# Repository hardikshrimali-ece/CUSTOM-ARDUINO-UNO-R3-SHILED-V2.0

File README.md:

# CUSTOM-ARDUINO-UNO-R3-SHILED-V2.0
Arduino UNO Universal Shield V2

User Manual & Developer Guide

Chapter 1 – Introduction

- Purpose of the shield
- Features
- Specifications
- Board overview
- Supported Arduino boards

Chapter 2 – Safety

- Reverse polarity protection
- Voltage limits
- Current limits
- Handling precautions

Chapter 3 – Hardware Layout

- Top view
- Bottom view
- Pin labels
- Connector locations
- Component locations

Chapter 4 – Pin Mapping

Feature| Arduino Pin
MAX7219 DIN| D11
MAX7219 CLK| D13
MAX7219 LOAD| D10
MAX7219 DOUT| D1
Buzzer| D9
SW1| D7
SW2| D6
SW3| D5
SW4| D4

Chapter 5 – Headers

- UART
- I2C
- SPI
- Analog
- Digital
- Power

Explain what every header is used for.

Chapter 6 – Example Programs

Example 1: MAX7219 Display Demo.
/*
  Arduino Shield V2.0
  Example 1 - MAX7219 Display Demo

  DIN  -> D11
  CLK  -> D13
  CS   -> D10
*/

#include <LedControl.h>

#define DIN_PIN 11
#define CLK_PIN 13
#define CS_PIN 10

LedControl lc = LedControl(DIN_PIN, CLK_PIN, CS_PIN, 1);

void setup()
{
  lc.shutdown(0, false);     // Wake display
  lc.setIntensity(0, 8);     // Brightness (0-15)
  lc.clearDisplay(0);
}

void loop()
{
  // Count from 0000 to 9999
  for (int i = 0; i <= 9999; i++)
  {
    displayNumber(i);
    delay(5);
  }

  delay(1000);

  // Display HELLO
  lc.clearDisplay(0);

  lc.setChar(0, 4, 'H', false);
  lc.setChar(0, 3, 'E', false);
  lc.setChar(0, 2, 'L', false);
  lc.setChar(0, 1, 'L', false);
  lc.setChar(0, 0, 'O', false);

  delay(3000);

  lc.clearDisplay(0);

  // Countdown
  for (int i = 9; i >= 0; i--)
  {
    lc.clearDisplay(0);
    lc.setDigit(0, 0, i, false);
    delay(500);
  }

  lc.clearDisplay(0);
}

void displayNumber(int number)
{
  lc.setDigit(0, 0, number % 10, false);
  lc.setDigit(0, 1, (number / 10) % 10, false);
  lc.setDigit(0, 2, (number / 100) % 10, false);
  lc.setDigit(0, 3, (number / 1000) % 10, false);
}

Example 2 – Button Test (D7, D6, D5, D4)
This example verifies that all four push buttons on your shield are working.

/*
  Arduino Shield V2.0
  Example 2 - Button Test

  Button 1 -> D7
  Button 2 -> D6
  Button 3 -> D5
  Button 4 -> D4
*/

#define BTN1 7
#define BTN2 6
#define BTN3 5
#define BTN4 4

void setup()
{
  Serial.begin(9600);

  pinMode(BTN1, INPUT_PULLUP);
  pinMode(BTN2, INPUT_PULLUP);
  pinMode(BTN3, INPUT_PULLUP);
  pinMode(BTN4, INPUT_PULLUP);

  Serial.println("=== Arduino Shield Button Test ===");
  Serial.println("Press any button...");
}

void loop()
{
  if (digitalRead(BTN1) == LOW)
  {
    Serial.println("Button 1 Pressed");
    delay(200);
  }

  if (digitalRead(BTN2) == LOW)
  {
    Serial.println("Button 2 Pressed");
    delay(200);
  }

  if (digitalRead(BTN3) == LOW)
  {
    Serial.println("Button 3 Pressed");
    delay(200);
  }

  if (digitalRead(BTN4) == LOW)
  {
    Serial.println("Button 4 Pressed");
    delay(200);
  }
}

Example 2 – reaction time game 
uses: 
 - 4 digit 7 segment display
 - buzzer
 - button 1 (D7)

 #include <LedControl.h>

#define DIN 11
#define CLK 13
#define CS 10

#define BUZZER 9
#define BUTTON 7

LedControl lc = LedControl(DIN, CLK, CS, 1);

unsigned long startTime;
unsigned long reaction;

void setup()
{
  pinMode(BUTTON, INPUT_PULLUP);
  pinMode(BUZZER, OUTPUT);

  lc.shutdown(0, false);
  lc.setIntensity(0, 8);
  lc.clearDisplay(0);

  randomSeed(analogRead(A0));
}

void loop()
{
  // Ready
  showText("GO");

  delay(2000);

  lc.clearDisplay(0);

  // Random wait
  delay(random(2000, 5000));

  // Beep
  tone(BUZZER, 1000, 150);

  // Show 0000
  displayNumber(0);

  startTime = millis();

  while (digitalRead(BUTTON) == HIGH);

  reaction = millis() - startTime;

  displayNumber(reaction);

  delay(5000);
}

void displayNumber(int num)
{
  lc.setDigit(0, 0, num % 10, false);
  lc.setDigit(0, 1, (num / 10) % 10, false);
  lc.setDigit(0, 2, (num / 100) % 10, false);
  lc.setDigit(0, 3, (num / 1000) % 10, false);
}

void showText(String txt)
{
  lc.clearDisplay(0);

  if (txt == "GO")
  {
    lc.setChar(0, 1, 'G', false);
    lc.setChar(0, 0, 'O', false);
  }
}

Example 4 - countdown timer 
uses: 
- display
- button 1
- buzzer

Chapter 7 – Libraries Required

- LedControl
- MD_MAX72XX
- SPI
- Wire

Explain why each library is used.

Chapter 8 – Troubleshooting

Troubleshooting Guide

The display does not turn ON

Possible reasons

- Arduino is not powered.
- Shield is not inserted properly.

What to do

1. Make sure the Arduino is powered.
2. Check that the shield is firmly connected.
3. Upload the example sketch again./*
  Arduino Shield V2.0
  Example 4 - Countdown Timer

  Button 1 -> Start Countdown
*/

#include <LedControl.h>

#define DIN     11
#define CLK     13
#define CS      10

#define BUTTON  7
#define BUZZER  9

LedControl lc = LedControl(DIN, CLK, CS, 1);

void setup()
{
  pinMode(BUTTON, INPUT_PULLUP);
  pinMode(BUZZER, OUTPUT);

  lc.shutdown(0, false);
  lc.setIntensity(0, 8);
  lc.clearDisplay(0);

  displayNumber(10);   // Initial countdown value
}

void loop()
{
  if (digitalRead(BUTTON) == LOW)
  {
    countdown(10);

    delay(1000);
  }
}

void countdown(int seconds)
{
  for (int i = seconds; i >= 0; i--)
  {
    displayNumber(i);
    delay(1000);
  }

  // Alarm
  for (int i = 0; i < 3; i++)
  {
    tone(BUZZER, 1000);
    delay(200);

    noTone(BUZZER);
    delay(200);
  }

  displayNumber(10);
}

void displayNumber(int num)
{
  lc.setDigit(0, 0, num % 10, false);
  lc.setDigit(0, 1, (num / 10) % 10, false);
  lc.setDigit(0, 2, (num / 100) % 10, false);
  lc.setDigit(0, 3, (num / 1000) % 10, false);
}

---

The display shows incorrect numbers

Possible reasons

- Incorrect program uploaded.
- Display initialization failed.

What to do

1. Restart the Arduino.
2. Upload the example program provided.
3. Ensure the display module is inserted correctly.

---

The buzzer does not make any sound

Possible reasons

- Buzzer disabled in the program.
- Buzzer is damaged.

What to do

1. Run the buzzer example program.
2. Restart the Arduino.
3. If there is still no sound, contact support.

---

Push buttons are not responding

Possible reasons

- Program is not running.
- Button is being pressed too quickly.

What to do

1. Restart the Arduino.
2. Press the button firmly once.
3. Test using the button example sketch.

---

I2C module is not working

What to do

1. Check that the sensor is connected to the I2C header.
2. Verify the sensor wiring.
3. Use an I2C Scanner sketch to detect the device.

---

UART module is not working

What to do

1. Ensure the TX and RX connections are correct.
2. Verify the baud rate in your program.
3. Restart both devices.

---

SPI module is not working

What to do

1. Ensure the module is connected to the SPI header.
2. Verify the program supports the connected module.
3. Restart the Arduino.

---

Arduino does not detect the shield

What to do

1. Remove the shield.
2. Reinsert it carefully.
3. Ensure all header pins are aligned correctly.

Board becomes hot

Warning
Disconnect power immediately.

Possible reasons

- Incorrect power supply.
- Short circuit.
- Incorrect wiring.

Do not continue using the board until the issue is identified.

Nothing works

1. Disconnect power.
2. Wait 10 seconds.
3. Reconnect power.
4. Upload the example sketch.
5. Test each feature one by one.

Please check the following:

- ✔ Arduino is powered.
- ✔ Shield is inserted correctly.
- ✔ Correct example sketch is uploaded.
- ✔ All modules are connected properly.
- ✔ USB cable is working.
- ✔ Arduino board is detected by the Arduino IDE.

If the problem still exists, provide:

- Shield version
- Arduino model
- Example program used
- Clear photos of the setup
- Description of the problem

Chapter 9 – PCB Features

- 2-layer PCB
- Reverse polarity protection
- Standard Arduino shield layout
- Stackable headers
- Universal expansion connectors

Chapter 10 – Revision History

V1.0

- Initial board

V2.0

- Added reverse polarity protection
- Added buzzer
- Added push buttons
- Added UART/I2C/SPI headers
- Improved layout

Chapter 11 – Future Expansion

- OLED
- NRF24L01
- GPS
- IMU
- Bluetooth
- Wi-Fi
- Sensors

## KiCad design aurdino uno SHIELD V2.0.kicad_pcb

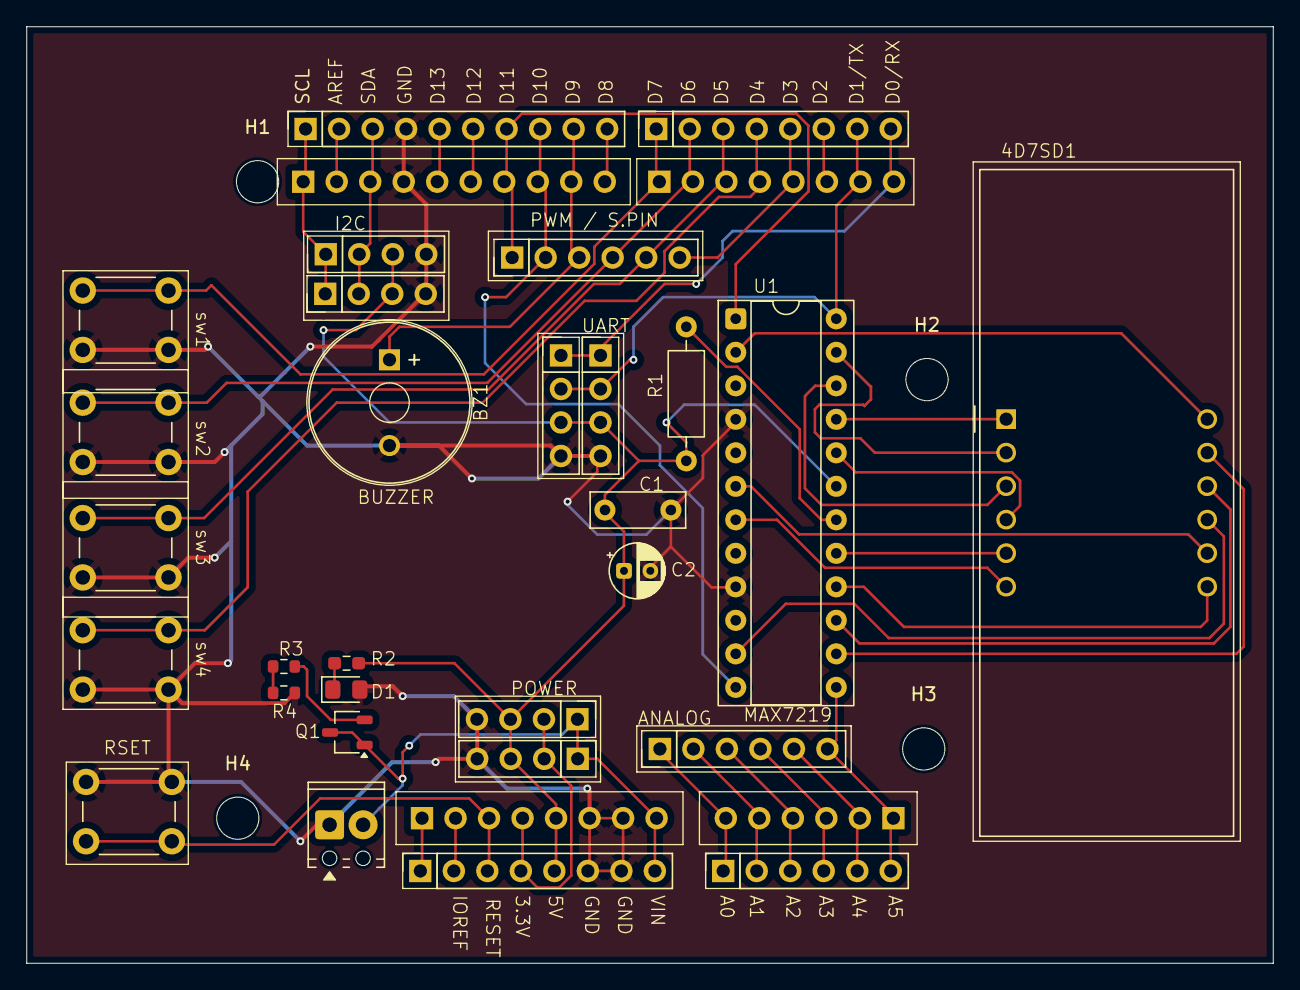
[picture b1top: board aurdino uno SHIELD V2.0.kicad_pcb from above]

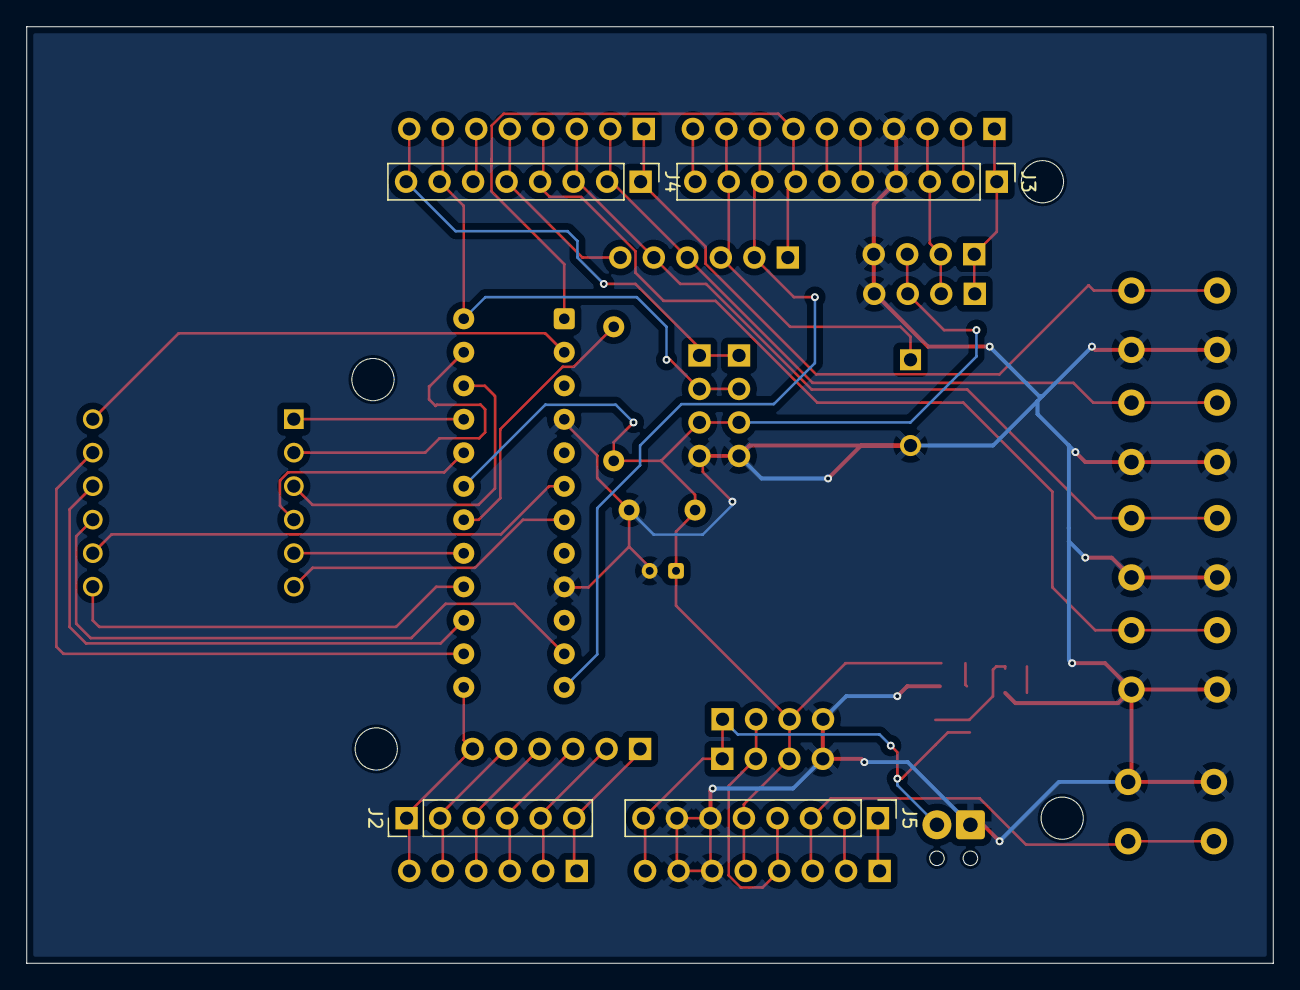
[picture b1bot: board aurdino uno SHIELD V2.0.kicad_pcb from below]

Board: 2 copper layers, 94.5 x 71.0 mm, 37 parts (4 on the bottom side), 43 nets.

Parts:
4D7SD1: CC56-12EWA; CA56-12EWA
BZ1: Buzzer; MagneticBuzzer_ProSignal_ABT-410-RC
C1: 0.1mF; C_Disc_D7.0mm_W2.5mm_P5.00mm
C2: 10mF; CP_Radial_D4.0mm_P2.00mm
D1: LED; LED_0805_2012Metric_Pad1.15x1.40mm_HandSolder
H1, H2, H3, H4: MountingHole; MountingHole_3.2mm_M3
I2C1, I2C2: I2C; PinHeader_1x04_P2.54mm_Vertical
J1: VIN 5V; TerminalBlock_Phoenix_MPT-0,5-2-2.54_1x02_P2.54mm_Horizontal
J2: ANALOG; PinHeader_1x06_P2.54mm_Vertical
J3: digital01; PinHeader_1x10_P2.54mm_Vertical
J4: digital02; PinHeader_1x08_P2.54mm_Vertical
J5: ANALOG01; PinHeader_1x08_P2.54mm_Vertical
J6: analog02; PinHeader_1x06_P2.54mm_Vertical
J7: digital01d; PinSocket_1x10_P2.54mm_Vertical
J8: digital02D; PinSocket_1x08_P2.54mm_Vertical
J9: ANALOG01D; PinSocket_1x08_P2.54mm_Vertical
J10: analog02; PinSocket_1x06_P2.54mm_Vertical
P1, P2, P3, P4: SW_Push; SW_PUSH_6mm_H5mm
PWR1, PWR2: I2C; PinHeader_1x04_P2.54mm_Vertical
Q1: PMOS_Substrate; TSOT-23
R1: 10k; R_Axial_DIN0207_L6.3mm_D2.5mm_P10.16mm_Horizontal
R2: 1.2k; R_0603_1608Metric_Pad0.98x0.95mm_HandSolder
R3: 100k; R_0603_1608Metric
R4: 100; R_0603_1608Metric
RSET1: SW_Push; SW_PUSH_6mm_H5mm
SPIN1: PWM; PinHeader_1x06_P2.54mm_Vertical
U1: MAX7219; DIP-24_W7.62mm_Socket
UART1, UART2: I2C; PinHeader_1x04_P2.54mm_Vertical

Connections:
3.3V: J5.4, J9.4, PWR1.2, PWR2.2
5V: C1.1, C2.1, I2C1.3, I2C2.3, J5.5, J9.5, PWR1.3, PWR2.3, R1.2, R2.2, U1.19 (V+), UART1.3, UART2.3
A0: J2.6, J6.1, J10.1
A1: J2.5, J6.2, J10.2
A2: J2.4, J6.3, J10.3
A3: J2.3, J6.4, J10.4
A4: J2.2, J6.5, J10.5
A5: J2.1, J6.6, J10.6, U1.13 (CLK)
D2: J4.6, J8.6
D3: J4.5, J8.5, SPIN1.6
D4: J4.4, J8.4, P4.1
D5: J4.3, J8.3, P3.1, SPIN1.5
D6: J4.2, J8.2, P2.1, SPIN1.4
D7: J4.1, J8.1, P1.1
D8: J3.10, J7.10
D9: BZ1.1 (+), J3.9, J7.9, SPIN1.3
D10: J3.8, J7.8, SPIN1.2, U1.12 (LOAD)
D11: J3.7, J7.7, SPIN1.1, U1.1 (DIN)
D12: J3.6, J7.6
D13: J3.5, J7.5
GND: BZ1.2 (-), C1.2, C2.2, D1.2 (A), I2C1.4, I2C2.4, J1.1, J3.4, J5.6, J5.7, J7.4, J9.6, J9.7, P1.2, P2.2, P3.2, P4.2, PWR1.4, PWR2.4, R4.1, RSET1.1, U1.4 (GND), U1.9 (GND), UART1.4, UART2.4
unnamed: 4D7SD1.12 (CC1), U1.2 (DIG_0)
unnamed: 4D7SD1.9 (CC2), U1.11 (DIG_1)
unnamed: 4D7SD1.8 (CC3), U1.6 (DIG_2)
unnamed: 4D7SD1.6 (CC4), U1.7 (DIG_3)
unnamed: 4D7SD1.3 (DPX), U1.22 (SEG_DP)
unnamed: 4D7SD1.11 (a), U1.14 (SEG_A)
unnamed: 4D7SD1.7 (b), U1.16 (SEG_B)
unnamed: 4D7SD1.4 (c), U1.20 (SEG_C)
unnamed: 4D7SD1.2 (d), U1.23 (SEG_D)
unnamed: 4D7SD1.1 (e), U1.21 (SEG_E)
unnamed: 4D7SD1.10 (f), U1.15 (SEG_F)
unnamed: 4D7SD1.5 (g), U1.17 (SEG_G)
unnamed: D1.1 (K), R2.1
unnamed: J5.3, J9.3, RSET1.2
unnamed: Q1.2 (G), R3.2
unnamed: R3.1, R4.2
unnamed: R1.1, U1.18 (ISET)
RX: J4.8, J8.8, UART1.1, UART2.1
SCL: I2C1.1, I2C2.1, J3.1, J7.1
SDA: I2C1.2, I2C2.2, J3.3, J7.3
TX: J4.7, J8.7, U1.24 (DOUT), UART1.2, UART2.2
VIN: J1.2, J5.8, J9.8, PWR1.1, PWR2.1, Q1.1 (D), Q1.3 (S)
